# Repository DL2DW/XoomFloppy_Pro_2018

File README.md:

# XoomFloppy Pro

## Introduction

After I had built the small [XoomFloppy](https://github.com/DL2DW/XoomFloppy_2018) in USB format, some people asked me if it is not possible to "make" one or the other connector on it.

I then developed the XoomFloppy Pro.  This is the full version of the ZoomFloppy. So also with IEEE-488 and parallel cable connection.

But for this version I decided to use the same IEEE-488 connector as for the PET and CBM devices. So as a platinum connector. Because with the Commodore drives there were always appropriate cables included, which use exactly this connection.

So one saves corresponding adapter solutions.

Otherwise, this is practically a replica of the ZoomFloppy, only much smaller, more compact and with the possibility to print out a corresponding housing.

# Technical

I basically just shrunk the ZoomFloppy. Otherwise, everything that applies to the ZoomFloppy also applies to the XoomFloppy Pro.

But the hardware base is otherwise the same. This is now the second device that is 100% compatible with the ZoomFloppy.

The core is the ATmega32u2, on which the original firmware of the ZoomFloppy is flashed. But also the driver module 7406 is present.

In the Docs folder I put a manual in German, which explains the assembly and the subsequent installation of the firmware.

# Case

I have designed a small case, which everyone is welcome to print out for themselves. With it, the XoomFloppy is also very well protected and simply looks better.

# BOM

The parts list consists of commercially available parts, which should actually be easy to obtain. If the housing is to be used, I recommend a 5mm round LED with the top flat. This will then fit flush into the housing.

|      | Description                                                  | Part                  | References          | Value                     | Footprint                                         | Quantity Per PCB |
| ---- | ------------------------------------------------------------ | --------------------- | ------------------- | ------------------------- | ------------------------------------------------- | ---------------- |
| 1    | Unpolarized capacitor                                        | C                     | C1 C5               | 100n                      | C_0805_2012Metric                                 | 2                |
| 2    | Unpolarized capacitor                                        | C                     | C4                  | 1µF                       | C_0805_2012Metric                                 | 1                |
| 3    | Unpolarized capacitor                                        | C                     | C2 C3               | 22pF                      | C_0805_2012Metric                                 | 2                |
| 4    | Generic connector, double row, 02x12, top/bottom pin numbering scheme (row 1: 1...pins_per_row, row2: pins_per_row+1 ... num_pins), script generated (kicad-library-utils/schlib/autogen/connector/) | Conn_02x12_Top_Bottom | CN4                 | IEEE-488 Port Stiftleiste | PinHeader_2x12_P2.54mm_Top_Bottom_Vertical_Mirror | 1                |
| 5    |                                                              | 618015231221          | CN3                 | Parallel Port             | 618015231221                                      | 1                |
| 6    | Light emitting diode                                         | LED                   | D1                  | LED Blue                  | LED_D3.0mm_Clear                                  | 1                |
| 7    | TVS.3 3.5pF [SOT-23-6]                                       | USBLC6-2SC6           | DZ1                 | USBLC6-2SC6               | SOT-23-6                                          | 1                |
| 8    | Resettable fuse, polymeric positive temperature coefficient  | Polyfuse              | F1                  | Polyfuse 1206L150         | Fuse_1206_3216Metric                              | 1                |
| 9    |                                                              | 7406D                 | IC1                 | 7406D                     | SOIC-14_3.9x8.7mm_P1.27mm                         | 1                |
| 10   | 6-pin DIN connector                                          | DIN-6                 | J1                  | IEC                       | DIN-6                                             | 1                |
| 11   | USB Micro Type B connector                                   | USB_B_Micro           | J2                  | USB_B_Micro               | USB_Micro-B_Wuerth_629105150521                   | 1                |
| 12   | Resistor                                                     | R                     | R2 R4 R6 R8 R10 R11 | 100k                      | R_0805_2012Metric                                 | 6                |
| 13   | Resistor                                                     | R                     | R15                 | 10k                       | R_0805_2012Metric                                 | 1                |
| 14   | Resistor                                                     | R                     | R13 R14             | 22                        | R_0805_2012Metric                                 | 2                |
| 15   | Resistor                                                     | R                     | R12                 | 220                       | R_0805_2012Metric                                 | 1                |
| 16   | Resistor                                                     | R                     | R1 R3 R5 R7 R9      | 4k7                       | R_0805_2012Metric                                 | 5                |
| 17   | 16MHz, 32kB Flash, 1kB SRAM, 1kB EEPROM, TQFP-32             | ATmega32U2-AU         | U1                  | ATmega32U2-AU             | TQFP-32_7x7mm_P0.8mm                              | 1                |
| 18   | Two pin crystal                                              | Crystal               | Y1                  | 16MHz                     | Crystal_SMD_5032-2Pin_5.0x3.2mm                   | 1                |

# PCB

The PCB can either be ordered directly from [PCBWay](https://www.pcbway.com/project/shareproject/XoomFloppy_Pro_1.html), or you can create it yourself from the Gerber files available here.

If you liked my project, I would be very happy about a small coffee donation.

# License

The contents of this repository, with the exception of the Docs and Software directories, are released under the following license:

- the "Creative Commons Attribution-NonCommercial-ShareAlike 4.0 International License" (CC BY-NC-SA 4.0) full text of this license is included in the [LICENSE.CC-NC-BY-SA-4.0](https://github.com/DL2DW/XoomFloppy_Pro_2018/blob/main/LICENSE.CC-NC-BY-SA) file and a copy can also be found at https://creativecommons.org/licenses/by-nc-sa/4.0/

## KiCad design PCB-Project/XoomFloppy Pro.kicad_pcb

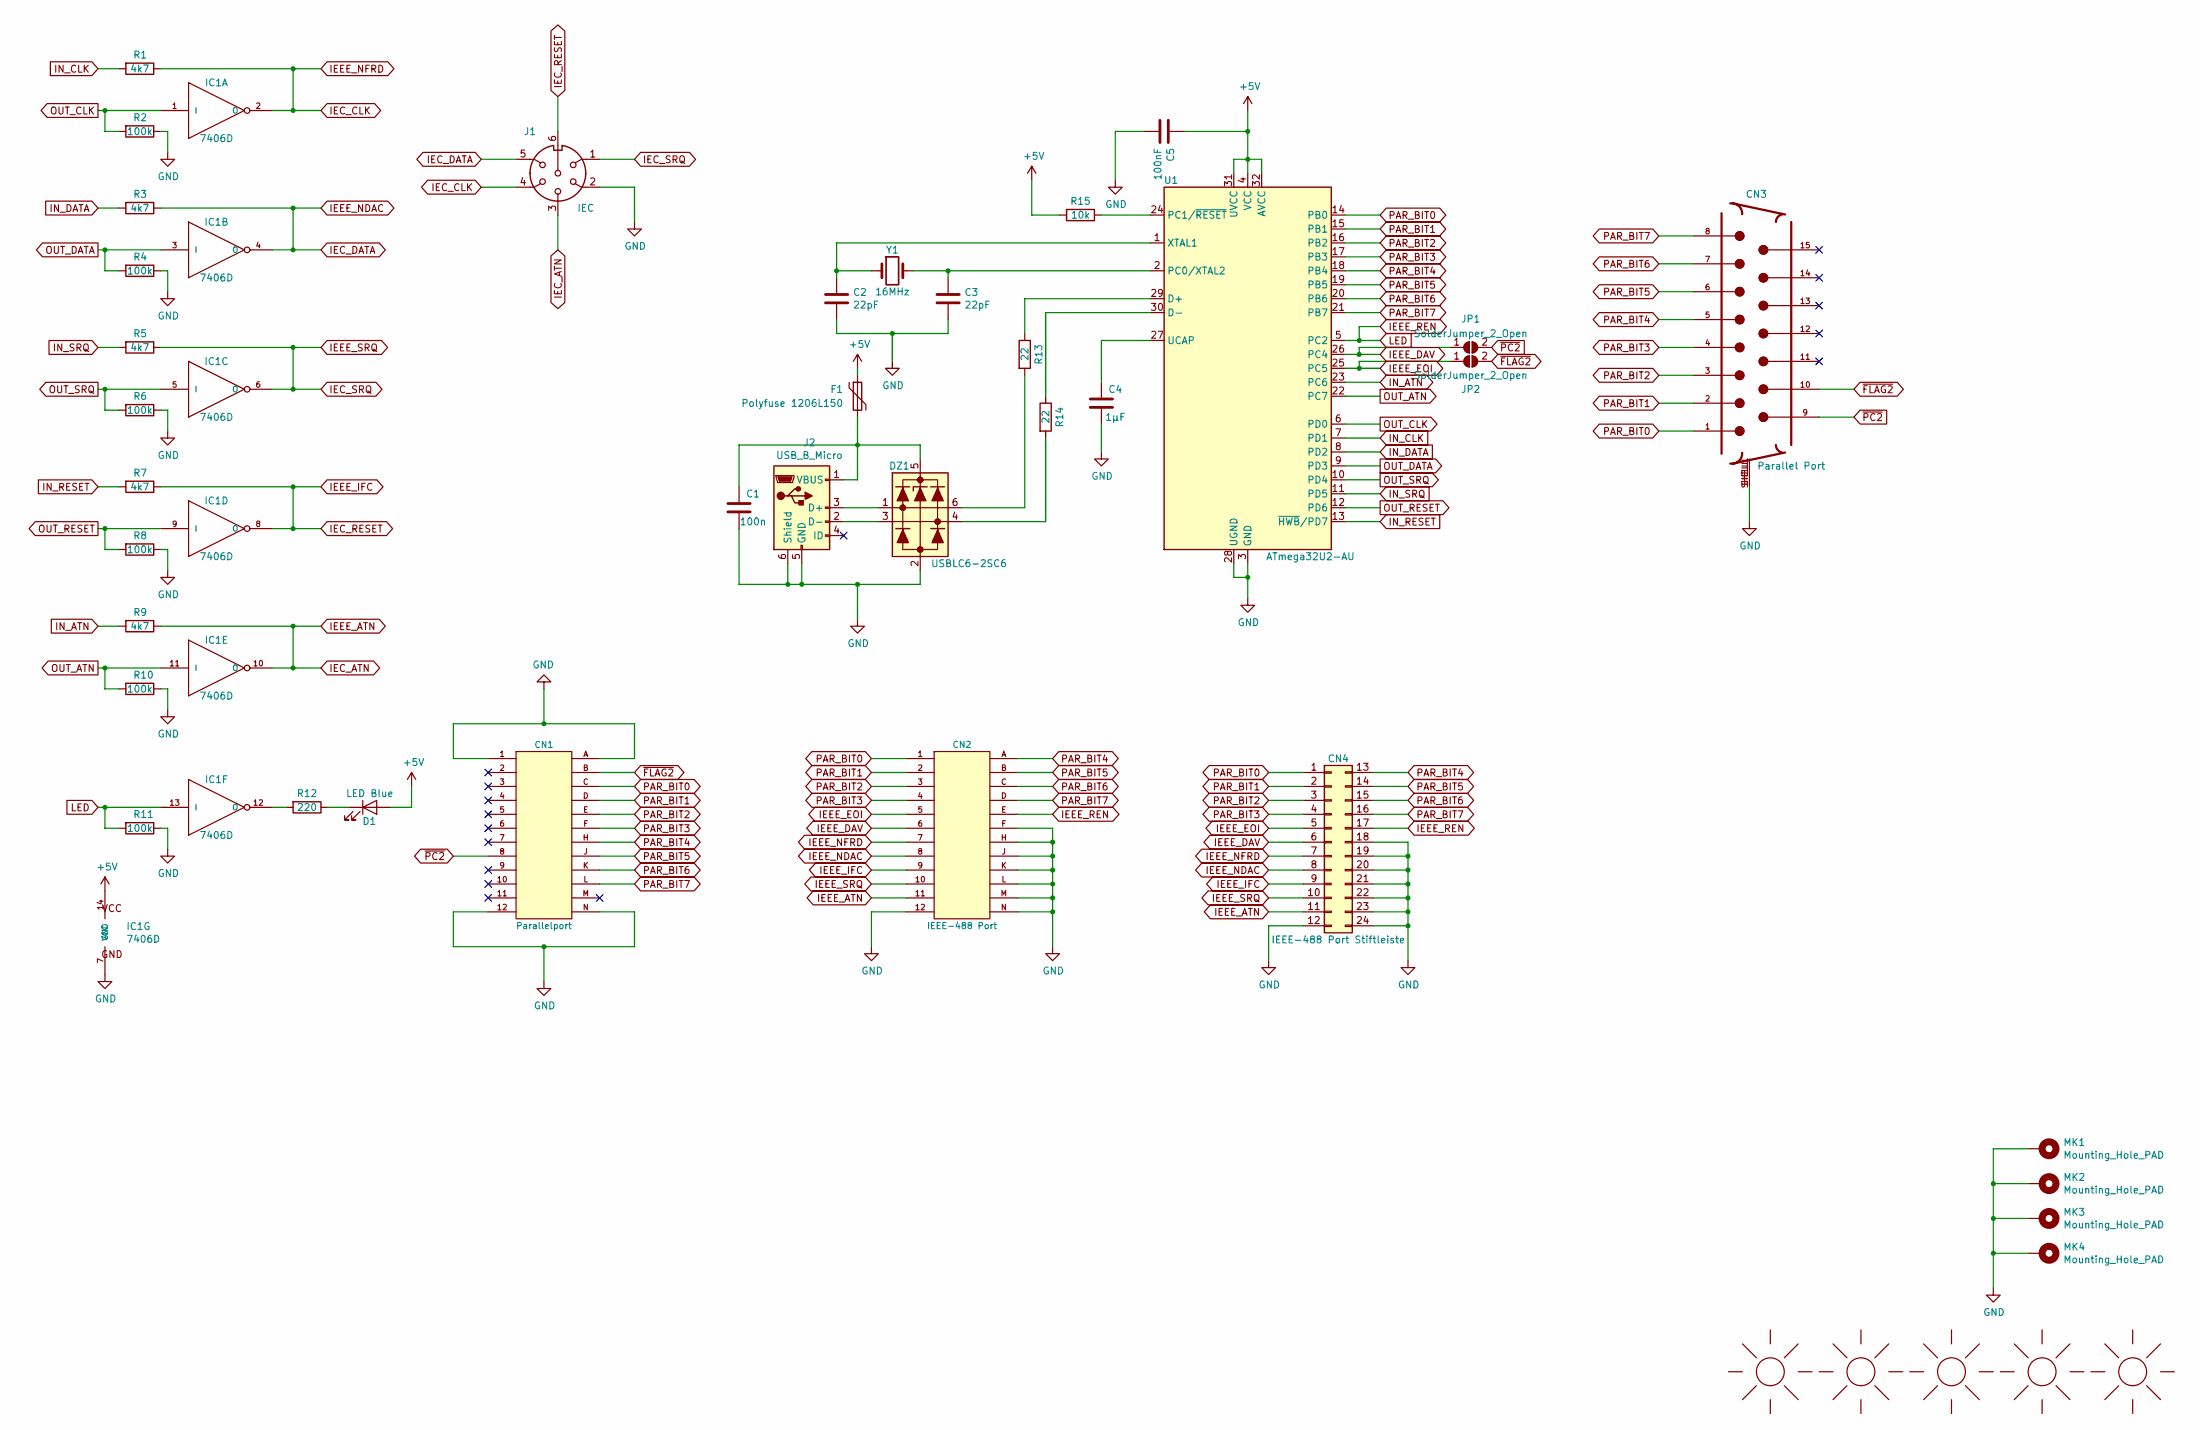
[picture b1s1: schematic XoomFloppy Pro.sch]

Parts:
C1: 100n; C_0805_2012Metric
C2, C3: 22pF; C_0805_2012Metric
C4: 1µF; C_0805_2012Metric
C5: 100nF; C_0805_2012Metric
CN1: Parallelport; Userport_Connector
CN2: IEEE-488 Port; Userport_Connector
CN3: Parallel Port; 618015231221
CN4: IEEE-488 Port Stiftleiste; PinHeader_2x12_P2.54mm_Top_Bottom_Vertical_Mirror
D1: LED Blue; LED_D3.0mm_Clear
DZ1: USBLC6-2SC6; SOT-23-6
F1: Polyfuse 1206L150; Fuse_1206_3216Metric
IC1: 7406D; SOIC-14_3.9x8.7mm_P1.27mm
J1: IEC; DIN-6
J2: USB_B_Micro; USB_Micro-B_Wuerth_629105150521
JP1, JP2: SolderJumper_2_Open; SolderJumper-2_P1.3mm_Open_RoundedPad1.0x1.5mm
M1: SUNLOGO; KiCad-Logo2_6mm_SilkScreen
M2: SUNLOGO; Logo_silk_CC-BY-NC-SA_10x3.6mm
M3: SUNLOGO; Logo_silk_OSHW_6x6mm
M4: SUNLOGO; DL2DW_Logo_Silk_20x10mm
M5: SUNLOGO; XoomFloppy Pro Schriftzug
MK1, MK2, MK3, MK4: Mounting_Hole_PAD; MountingHole_3.2mm_M3
R1, R3, R5, R7, R9: 4k7; R_0805_2012Metric
R2, R4, R6, R8, R10, R11: 100k; R_0805_2012Metric
R12: 220; R_0805_2012Metric
R13, R14: 22; R_0805_2012Metric
R15: 10k; R_0805_2012Metric
U1: ATmega32U2-AU; TQFP-32_7x7mm_P0.8mm
Y1: 16MHz; Crystal_SMD_5032-2Pin_5.0x3.2mm

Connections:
+5V: C5.2, D1.2 (A), F1.1, IC1.14 (VCC), R15.2, U1.4 (VCC), U1.31 (UVCC), U1.32 (AVCC)
GND: C1.1, C2.2, C3.2, C4.1, C5.1, CN1.1, CN1.12, CN1.A, CN1.N, CN2.12, CN2.F, CN2.H, CN2.J, CN2.K, CN2.L, CN2.M, CN2.N, CN3.SHELL (SHIELD), CN3.SHELL1 (SHIELD), CN4.12, CN4.18, CN4.19, CN4.20, CN4.21, CN4.22, CN4.23, CN4.24, DZ1.2, IC1.7 (GND), J1.2, J2.5 (GND), J2.6 (Shield), MK1.1, MK2.1, MK3.1, MK4.1, R2.1, R4.1, R6.1, R8.1, R10.1, R11.1, U1.3 (GND), U1.28 (UGND)
IEC_ATN: CN2.11, CN4.11, IC1.10 (O), J1.3, R9.1
IEC_CLK: CN2.7, CN4.7, IC1.2 (O), J1.4, R1.1
IEC_DATA: CN2.8, CN4.8, IC1.4 (O), J1.5, R3.1
IEC_RESET: CN2.9, CN4.9, IC1.8 (O), J1.6, R7.1
IEC_SRQ: CN2.10, CN4.10, IC1.6 (O), J1.1, R5.1
IEEE_DAV: CN2.6, CN4.6, JP1.1 (A), U1.26 (PC4)
IEEE_EOI: CN2.5, CN4.5, JP2.1 (A), U1.25 (PC5)
IEEE_REN: CN2.E, CN4.17, IC1.13 (I), R11.2, U1.5 (PC2)
IN_ATN: R9.2, U1.23 (PC6)
IN_CLK: R1.2, U1.7 (PD1)
IN_DATA: R3.2, U1.8 (PD2)
IN_RESET: R7.2, U1.13 (~HWB~/PD7)
IN_SRQ: R5.2, U1.11 (PD5)
unnamed: C1.2, DZ1.5, F1.2, J2.1 (VBUS)
unnamed: C2.1, U1.1 (XTAL1), Y1.1
unnamed: C3.1, U1.2 (PC0/XTAL2), Y1.2
unnamed: C4.2, U1.27 (UCAP)
unnamed: D1.1 (K), R12.1
unnamed: DZ1.1, J2.3 (D+)
unnamed: DZ1.3, J2.2 (D-)
unnamed: DZ1.4, R14.2
unnamed: DZ1.6, R13.2
unnamed: IC1.12 (O), R12.2
unnamed: R13.1, U1.29 (D+)
unnamed: R14.1, U1.30 (D-)
unnamed: R15.1, U1.24 (PC1/~RESET)
OUT_ATN: IC1.11 (I), R10.2, U1.22 (PC7)
OUT_CLK: IC1.1 (I), R2.2, U1.6 (PD0)
OUT_DATA: IC1.3 (I), R4.2, U1.9 (PD3)
OUT_RESET: IC1.9 (I), R8.2, U1.12 (PD6)
OUT_SRQ: IC1.5 (I), R6.2, U1.10 (PD4)
PAR_BIT0: CN1.C, CN2.1, CN3.1, CN4.1, U1.14 (PB0)
PAR_BIT1: CN1.D, CN2.2, CN3.2, CN4.2, U1.15 (PB1)
PAR_BIT2: CN1.E, CN2.3, CN3.3, CN4.3, U1.16 (PB2)
PAR_BIT3: CN1.F, CN2.4, CN3.4, CN4.4, U1.17 (PB3)
PAR_BIT4: CN1.H, CN2.A, CN3.5, CN4.13, U1.18 (PB4)
PAR_BIT5: CN1.J, CN2.B, CN3.6, CN4.14, U1.19 (PB5)
PAR_BIT6: CN1.K, CN2.C, CN3.7, CN4.15, U1.20 (PB6)
PAR_BIT7: CN1.L, CN2.D, CN3.8, CN4.16, U1.21 (PB7)
~FLAG2: CN1.B, CN3.10, JP2.2 (B)
~PC2: CN1.8, CN3.9, JP1.2 (B)

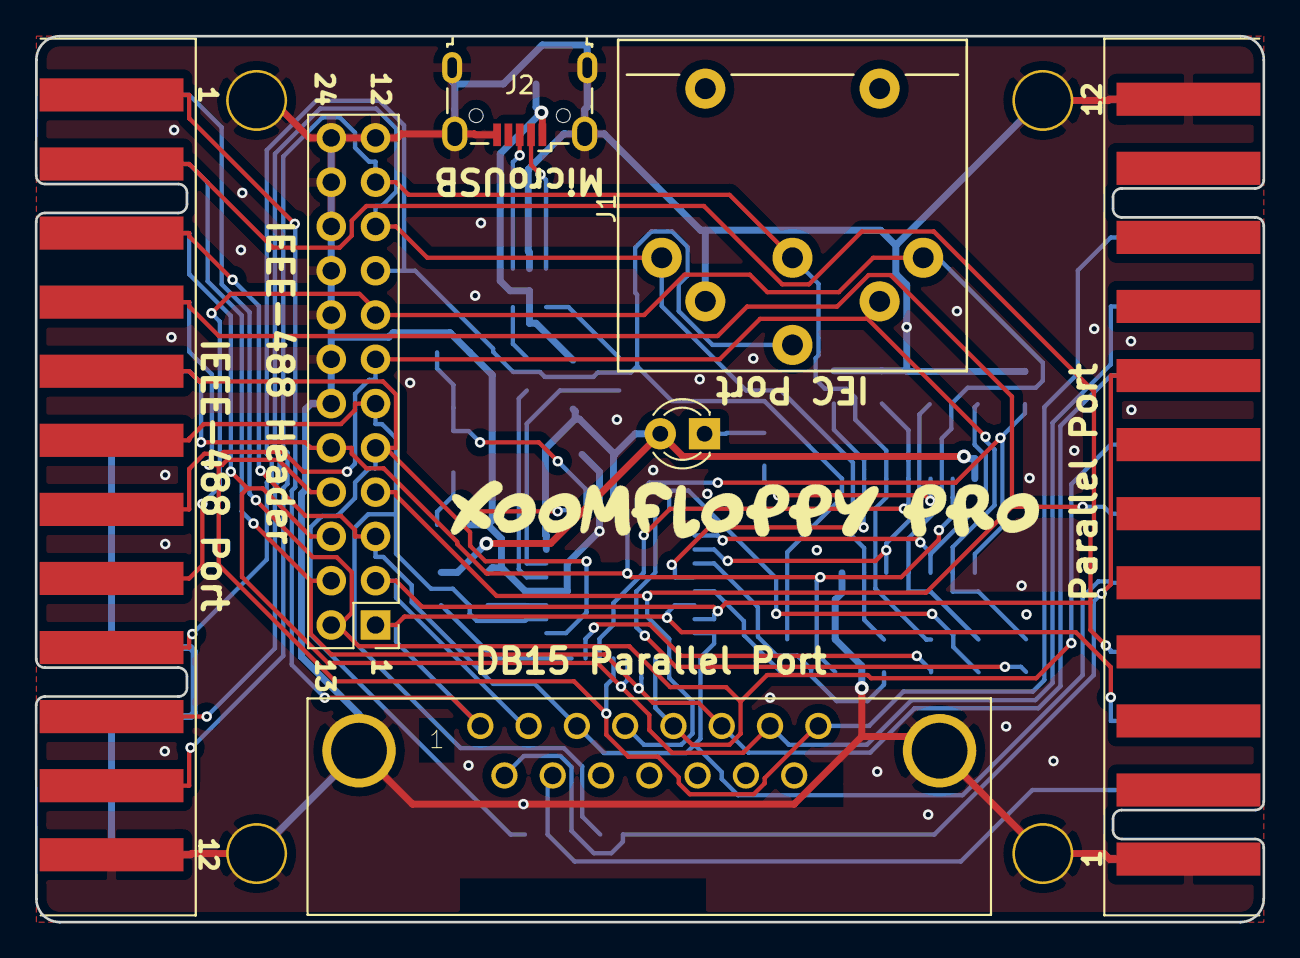
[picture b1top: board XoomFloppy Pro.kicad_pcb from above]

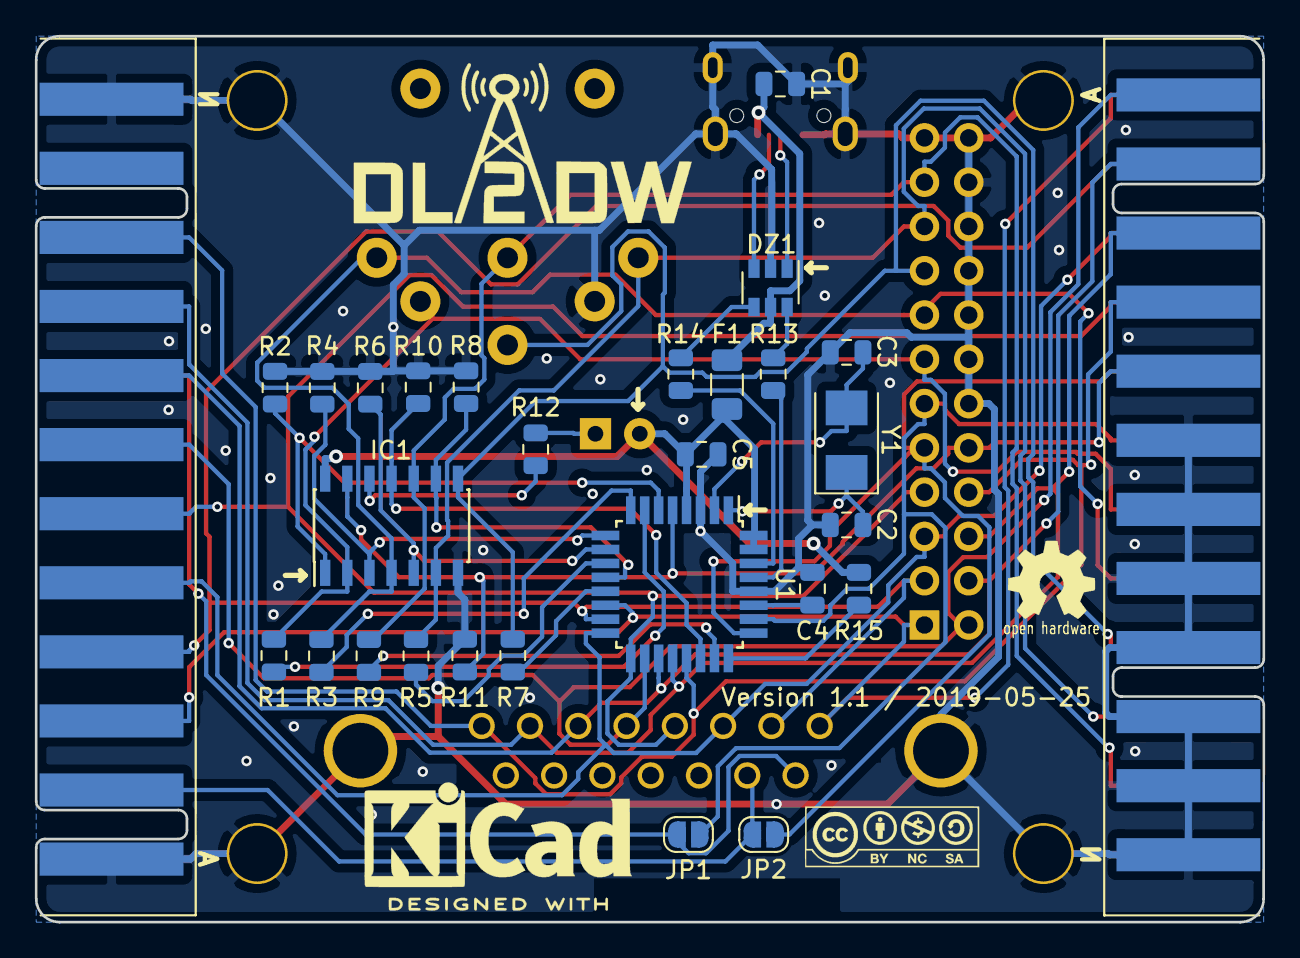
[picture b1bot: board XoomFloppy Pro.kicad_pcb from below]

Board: 2 copper layers, 70.4 x 50.8 mm, 43 parts (31 on the bottom side), 43 nets.

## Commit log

2021-01-06 PCB order link added
